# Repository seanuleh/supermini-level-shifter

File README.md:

# Hyper Level Shifter

A simple through-hole PCB that pairs an ESP32-S3 Super Mini with a SN74AHCT125N quad bus buffer to shift 3.3V GPIO signals up to 5V logic — designed for driving WS2812B/SK6812 LED strips with [Hyperk](https://github.com/awawa-dev/Hyperk) / [HyperHDR](https://github.com/awawa-dev/HyperHDR) ambilight setups.

<table><tr>
<td></td>
<td></td>
</tr><tr>
<td align="center">Front</td>
<td align="center">Back</td>
</tr></table>

**[Download Gerbers (ZIP)](https://github.com/seanuleh/supermini-level-shifter/raw/main/manufacturing/default/default.gerber.zip)** — ready for JLCPCB / PCBWay (order bare PCB only)

## Features

- Socket for ESP32-S3 Super Mini (2× 1×9 female 2.54mm headers)
- DIP-14 socket for SN74AHCT125N logic level shifter (3.3V → 5V)
- Dual 3-pin 2.54mm screw terminals (top + bottom — choose whichever orientation suits your wiring)
- 68Ω series resistors on data outputs for signal integrity
- 100nF decoupling capacitor on IC VCC
- All through-hole components — no SMD soldering required

## Screw Terminal Pinout

Both terminals are electrically identical:

| Pin | Signal | Description |
|-----|--------|-------------|
| 1   | DATA1  | GP1 level-shifted (5V logic) — LED segment 1 |
| 2   | DATA2  | GP2 level-shifted (5V logic) — LED segment 2 |
| 3   | GND    | Ground reference |

> Power (5V) for the LED strips should come from a dedicated 5V supply, not the ESP32.

## Signal Path

```
ESP32 GP1 (3.3V) → SN74AHCT125N 1A → 1Y → 68Ω → Terminal pin 1
ESP32 GP2 (3.3V) → SN74AHCT125N 2A → 2Y → 68Ω → Terminal pin 2
ESP32 GND ──────────────────────────────────────→ Terminal pin 3
ESP32 5V  ──────────────────────────────────────→ IC VCC (pin 14)
```

## BOM

All parts are hand-soldered. No JLCPCB assembly required — order the bare PCB only.

| Ref | Part | Notes |
|-----|------|-------|
| J1, J2 | 1×9 female 2.54mm pin header | 2× required |
| U1 | SN74AHCT125N | DIP-14, e.g. LCSC C5907 |
| — | DIP-14 IC socket | Order separately |
| J3, J4 | 3-pin 2.54mm screw terminal | e.g. KF128-2.54-3P, Phoenix MPT-0.5/3-2.54 |
| R1, R2 | 68Ω 1/8W axial resistor | Any 62–100Ω 1/8W axial |
| C1 | 100nF ceramic disc capacitor | 50V, 2.5mm pitch |

## Assembly Notes

- Install the DIP-14 socket first, then insert the SN74AHCT125N IC into the socket
- ESP32-S3 Super Mini plugs into J1/J2 with USB-C port facing toward the "USB Port ↑" silkscreen label
- The decoupling cap (C1) is non-polarised — orientation doesn't matter
- LED strip power should come from a dedicated 5V PSU; the ESP32 5V pin cannot source enough current for a full TV ambilight run

## Project Structure

Built with [atopile](https://atopile.io) 0.15.x.

```
ato.yaml                        # Build config
elec/src/
  level_shifter.ato             # Top-level module
  esp32s3_super_mini.ato        # ESP32 socket module
  parts/
    Header1x9F/                 # 1×9 female header
    SN74AHCT125N/               # DIP-14 quad buffer
    ScrewTerminal_2.54_3P/      # 3-pin screw terminal
    Resistor_TH_68R/            # 68Ω axial resistor
    Capacitor_TH_100nF/         # 100nF ceramic disc cap
elec/layouts/default/           # KiCAD PCB layout
```

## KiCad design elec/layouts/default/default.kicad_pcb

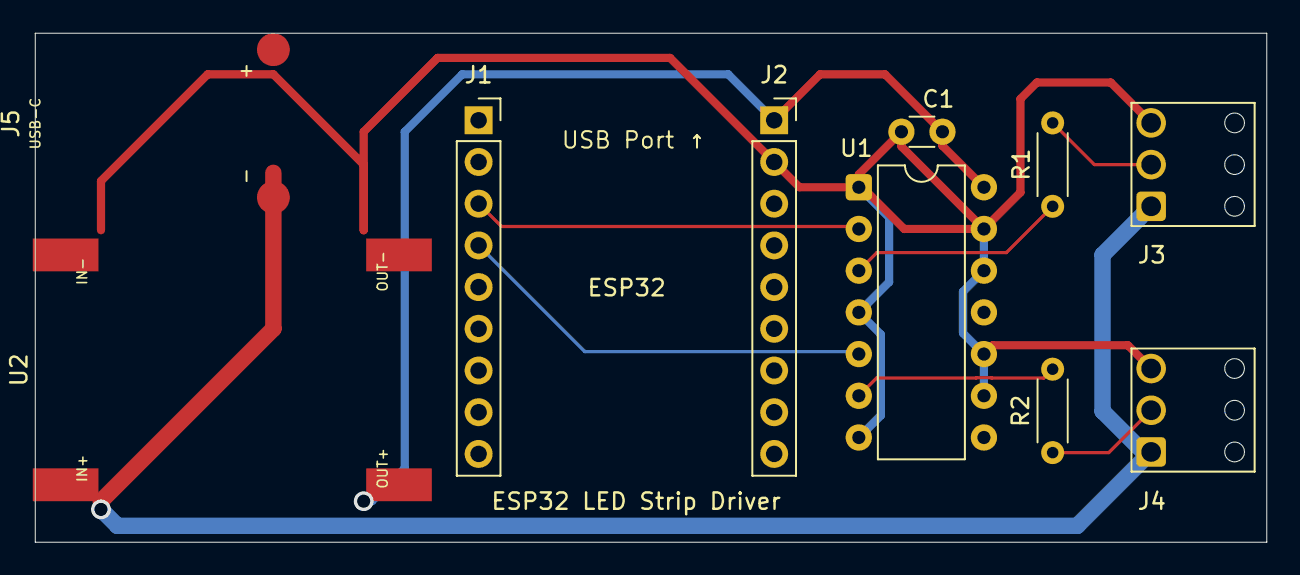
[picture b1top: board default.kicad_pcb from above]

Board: 2 copper layers, 75.0 x 31.0 mm, 10 parts (0 on the bottom side), 9 nets.

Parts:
C1: C_Disc_D3.0mm_W1.6mm_P2.50mm
J1, J2: PinSocket_1x09_P2.54mm_Vertical
J3, J4: KF141R_3P
J5: PDTrigger_Direct
R1, R2: R_Axial_DIN0204_L3.6mm_D1.6mm_P5.08mm_Horizontal
U1: DIP-14_W7.62mm
U2: BuckModule_5V_Direct

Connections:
1: J3.1, J4.1, J5.1, U2.1
1-1: R1.1, U1.3
1-2: R2.1, U1.6
2: J1.3, U1.2
2-1: J3.2, R1.2
2-2: J4.2, R2.2
5: J1.4, U1.5
gnd: C1.2, J2.2, J3.3, J4.3, J5.2, U1.1, U1.4, U1.7, U1.9, U1.10, U1.12, U1.13, U2.2, U2.4
vcc_5v: C1.1, J2.1, U1.14, U2.3

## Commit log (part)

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2026-05-08 Fix link case sensitivity in README.md
2026-05-29 fix: power modules
2026-05-30 feat: completed and ordered
